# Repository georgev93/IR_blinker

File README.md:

# IR Blinker

## Programming Connection

The programming tab shown at the bottom of the rendering above (which can be cut off after flashing for minimal final board size!) can be connected to a PIC programmer (such as a PICkit or ICD) via a Tag-Connect cable. The Tag-Connect cable should be a 6-pin no-legs variant such as [this one](https://www.tag-connect.com/product/tc2030-pkt-nl-6-pin-no-legs-cable-for-microchip-pickit-3) that connects to a [PICkit 3](https://www.microchip.com/en-us/development-tool/pg164130). A [retention clip](https://www.tag-connect.com/product/tc2030-retaining-clip-board-3-pack) for the no-leg Tag-connect connector makes life very easy. Lastly, if you lose your retention clips, you might want to invest in a [state-of-the-art-and-absolutely-not-just-a-paperclip retention clip holder](https://www.tag-connect.com/product/tc20x0-cliphanger).

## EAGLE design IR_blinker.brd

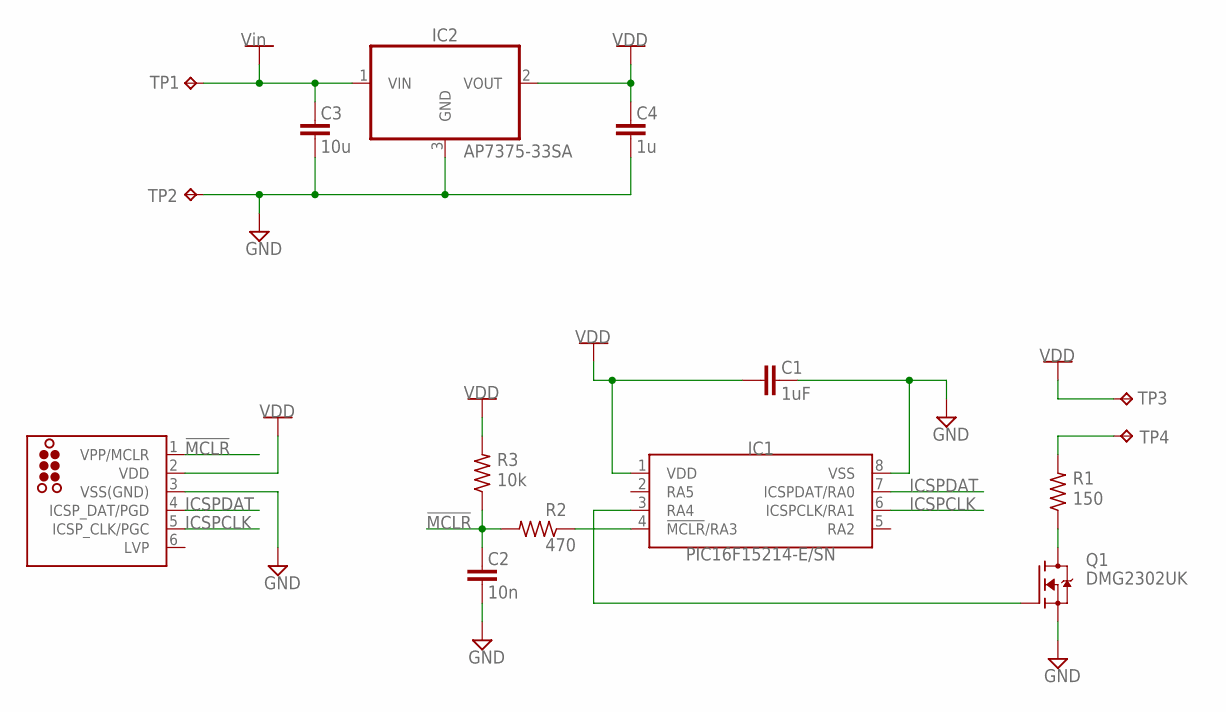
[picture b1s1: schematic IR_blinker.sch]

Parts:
C1: 1uF; C0603
C2: 10n; C0603
C3: 10u; C0603
C4: 1u; C0603
IC1: PIC16F15214-E/SN; SOIC-8
IC2: AP7375-33SA; SOT23
J1: TC2030-MCP-NL
Q1: DMG2302UK; SOT23
R1: 150; R0603
R2: 470; R0603
R3: 10k; R0603
TP1, TP2, TP3, TP4: TPTP20SQ; TP20SQ

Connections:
!MCLR: C2.2, J1.1 (VPP/MCLR), R2.2, R3.1
GND: C1.2, C2.1, C3.1, C4.1, IC1.8 (VSS), IC2.3 (GND), J1.3 (VSS(GND)), Q1.2 (S), TP2.TP
ICSPCLK: IC1.6 (ICSPCLK/RA1), J1.5 (ICSP_CLK/PGC)
ICSPDAT: IC1.7 (ICSPDAT/RA0), J1.4 (ICSP_DAT/PGD)
LED_RETURN: R1.2, TP4.TP
unnamed: Q1.3 (D), R1.1
unnamed: IC1.3 (RA4), Q1.1 (G)
unnamed: IC1.4 (!MCLR!/RA3), R2.1
VDD: C1.1, C4.2, IC1.1 (VDD), IC2.2 (VOUT), J1.2 (VDD), R3.2, TP3.TP
VIN: C3.2, IC2.1 (VIN), TP1.TP

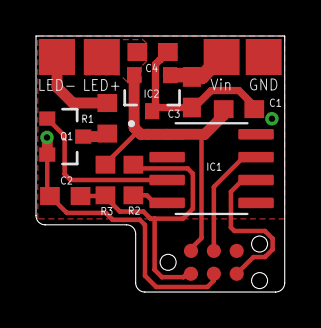
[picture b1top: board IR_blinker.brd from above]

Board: 2 copper layers, 13.8 x 14.2 mm, 15 parts (0 on the bottom side), 10 nets.

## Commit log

2022-11-20 First swipe (no regulator)
2022-11-24 Linear Regulator added. Passives added to MCLR.
2022-12-03 Adding BOM, readme, and cam file
2022-12-03 Updating README
2023-01-03 Adding schematic and layout pdfs (and images to the README)
2023-01-11 Adding image to README to describe nets

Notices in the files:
parts and their libraries:
tag_connect: ©2009 ROFA.cz - modified and updated by Robert Darlington ‹rdarlington@gmail.com›
